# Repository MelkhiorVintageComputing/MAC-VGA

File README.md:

# Mac (vintage) to VGA adapter

To plug a VGA monitor on a vintage Mac with the DB15 connector.

See https://github.com/sfiera/mactech/blob/master/displays.rst for a lot of informations on the subject.

This was designed for my own use, the only goal was 'easy to solder'. Includes a basic 3D-printed two-parts shell to protect the adapter.

Works for me to get all possible resolutions on both a Quadra 650 and a LC III.

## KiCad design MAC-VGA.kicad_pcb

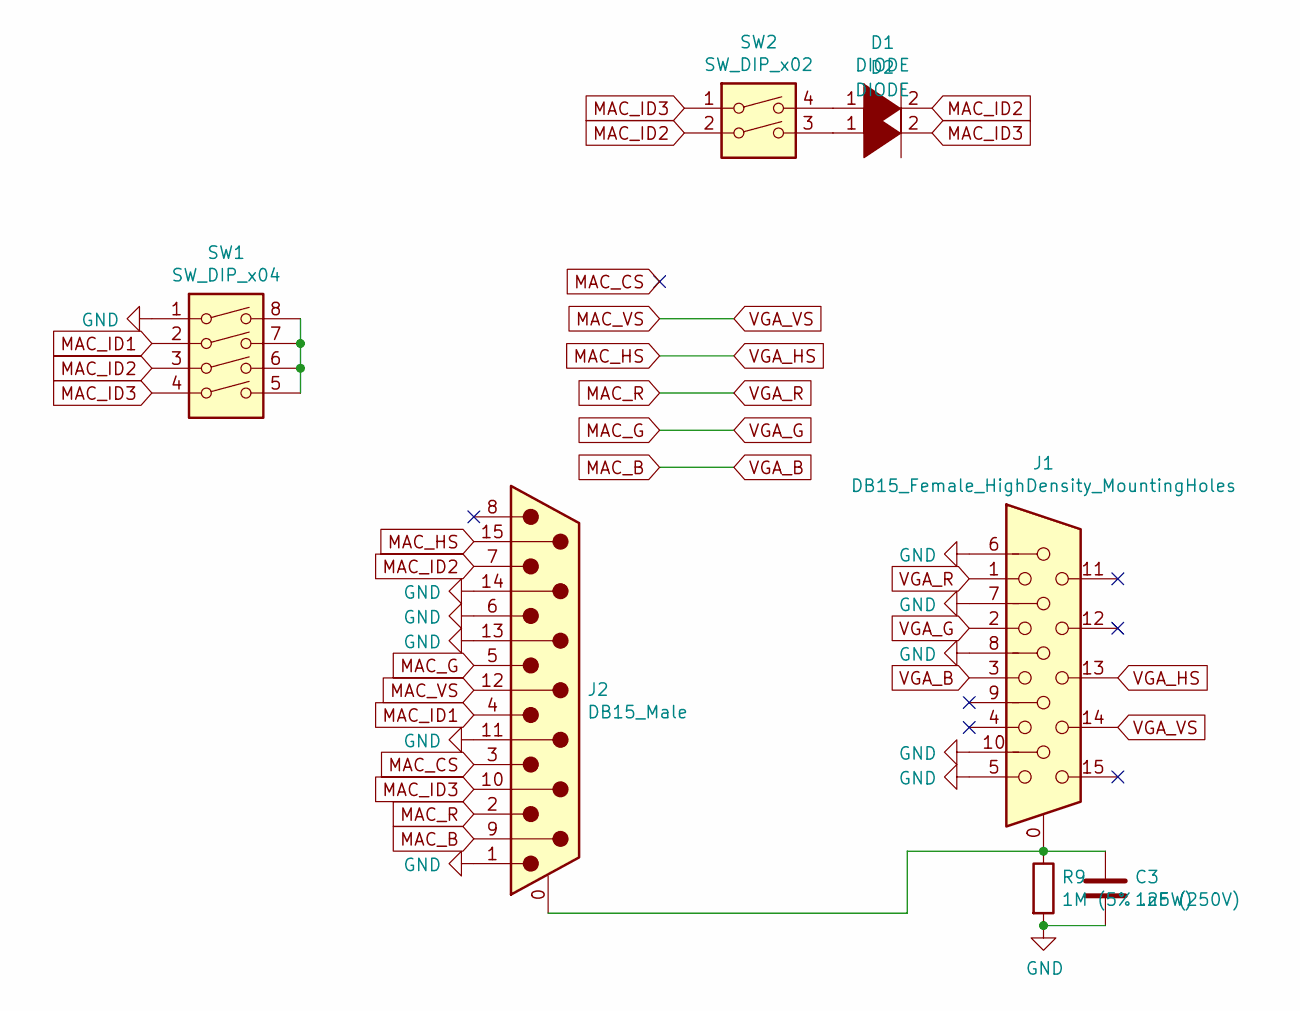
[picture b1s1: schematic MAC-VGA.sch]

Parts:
C3: 1nF (250V); CP_Radial_D6.3mm_P2.50mm; MPN 860021373002
D1, D2: DIODE; D_DO-35_SOD27_P2.54mm_Vertical_AnodeUp; MPN 1N4148
J1: DB15_Female_HighDensity_MountingHoles; L77HDE15SD1CH4RHNVGA; MPN L77HDE15SD1CH4RHNVGA
J2: DB15_Male; DSUB-15_Male_Horizontal_P2.77x2.84mm_EdgePinOffset7.70mm_Ho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; MPN L717SDA15PA4CH4R
R9: 1M (5% .25W); R_Axial_DIN0207_L6.3mm_D2.5mm_P2.54mm_Vertical; MPN MFR50SFTE52-1M
SW1: SW_DIP_x04; SW_DIP_SPSTx04_Slide_6.7x11.72mm_W7.62mm_P2.54mm_LowProfile; MPN 210-4MS
SW2: SW_DIP_x02; SW_DIP_SPSTx02_Slide_6.7x6.64mm_W7.62mm_P2.54mm_LowProfile; MPN 210-2MS

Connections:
GND: C3.2, J1.5, J1.6, J1.7, J1.8, J1.10, J2.1, J2.6, J2.11 (P111), J2.13, J2.14, R9.2, SW1.1
MAC_B: J1.3, J2.9
MAC_CS: J2.3
MAC_G: J1.2, J2.5
MAC_HS: J1.13, J2.15
MAC_ID1: J2.4, SW1.2
MAC_ID2: D1.2 (A), J2.7, SW1.3, SW2.2
MAC_ID3: D2.2 (A), J2.10, SW1.4, SW2.1
MAC_R: J1.1, J2.2
MAC_VS: J1.14, J2.12
unnamed: C3.1, J1.0, J2.0 (PAD), R9.1
unnamed: D1.1 (K), SW2.4
unnamed: D2.1 (K), SW2.3
unnamed: SW1.5, SW1.6, SW1.7, SW1.8

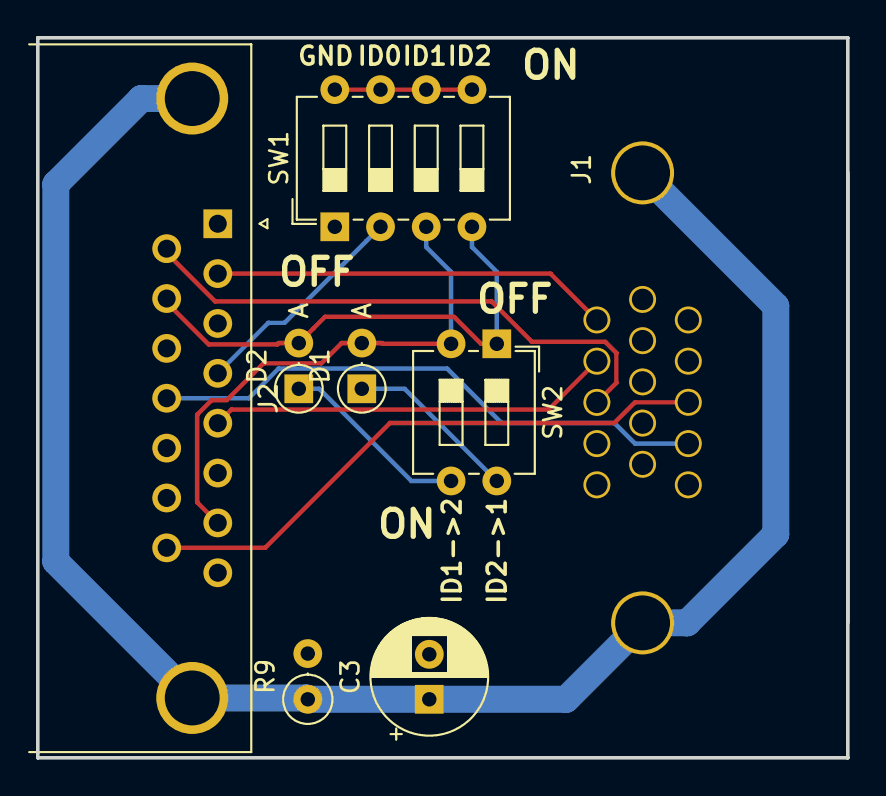
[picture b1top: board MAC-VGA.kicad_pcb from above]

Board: 2 copper layers, 45.0 x 40.0 mm, 8 parts (0 on the bottom side), 13 nets.

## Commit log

2023-10-05 license
